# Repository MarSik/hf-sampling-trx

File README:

HF RX based on QSD and class E TX
---------------------------------

Important components:

Si570 - any frequency I2C controlled square wave oscillator
74CBT(LV)3253 - dual 1:4 analog multiplexor
LT6231CS8 - ultra low noise (1.1nV/sqrtHz) opamp
ATXmega128A3U - 8bit micro with dual ADC and DAC
XC9572XL - CPLD, programmable logic, 3.3V

References:

- Dan Tayloe, N7VE
  Ultra Low Noise, High Performance, Zero IF Quadrature Product Detector and Preamplifier
  http://www.norcalqrp.org/files/Tayloe_mixer_x3a.pdf

- Gerald Youngblood, AC5OG
  A Software-Defined Radio for the Masses
  http://www.flex-radio.com/data/doc/qex1.pdf
  http://www.flex-radio.com/data/doc/qex2.pdf
  http://www.flex-radio.com/data/doc/qex3.pdf
  http://www.flex-radio.com/data/doc/qex4.pdf

- YU1LM
  HF - 6m band pass filters
  http://yu1lm.qrpradio.com/HF-6m%20BP%20YU1LM%20ver2.pdf

- Dan Tayloe, N7VE
  Class E Amplifiers - NorCal QRP Club
  http://www.norcalqrp.org/files/class_e_amplifiers.pdf

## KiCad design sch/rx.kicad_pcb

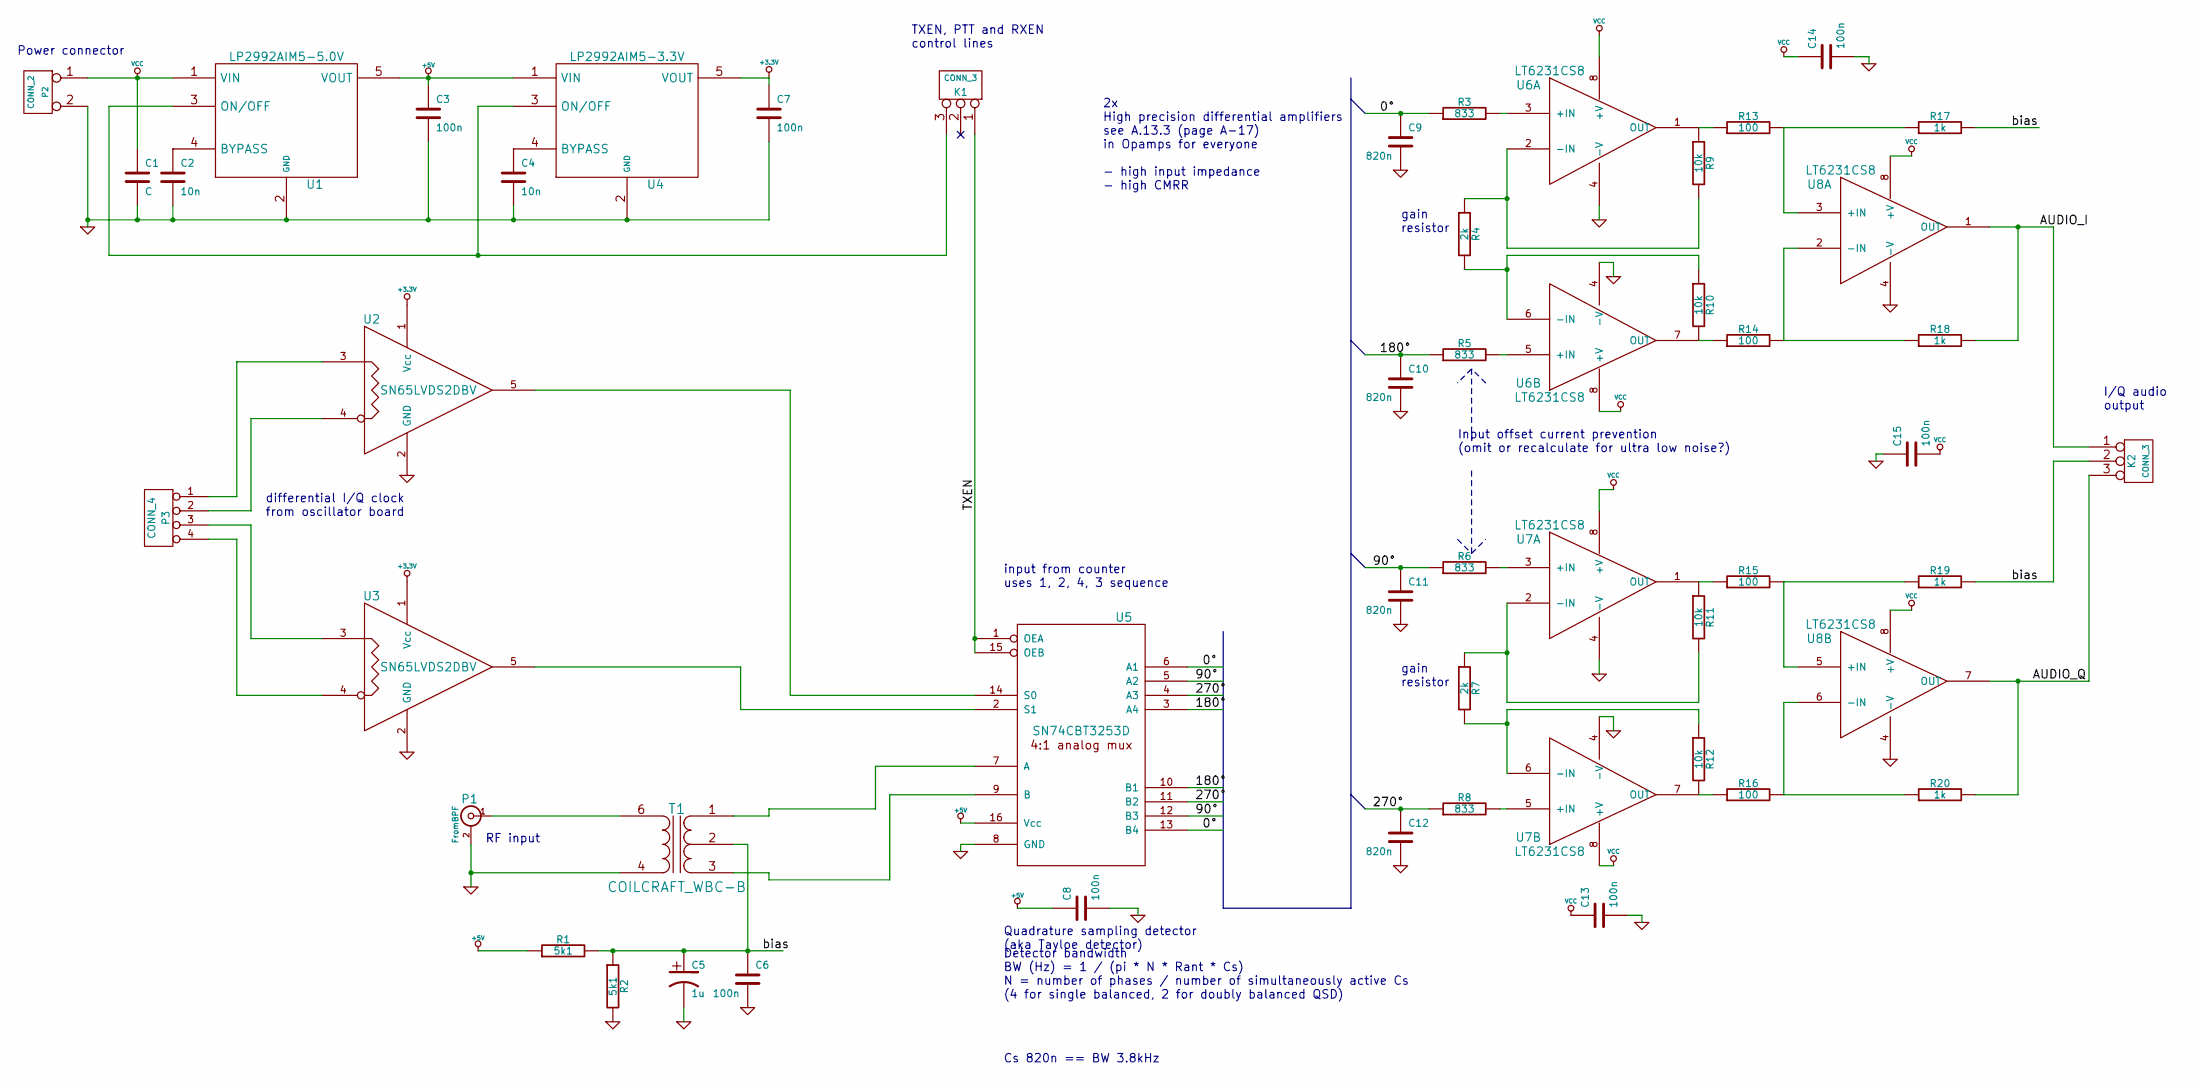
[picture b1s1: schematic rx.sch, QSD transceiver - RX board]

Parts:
C1: C
C2, C4: 10n
C3, C6, C7, C8, C13, C14, C15: 100n
C5: 1u
C9, C10, C11, C12: 820n
K1, K2: CONN_3
P1: FromBPF
P2: CONN_2
P3: CONN_4
R1, R2: 5k1
R3, R5, R6, R8: 833
R4, R7: 2k
R9, R10, R11, R12: 10k
R13, R14, R15, R16: 100
R17, R18, R19, R20: 1k
T1: COILCRAFT_WBC-B
U1: LP2992AIM5-5.0V; SOT23-5; Part Number LP2992AIM5-3.3CT-ND
U2, U3: SN65LVDS2DBV
U4: LP2992AIM5-3.3V; SOT23-5; Part Number LP2992AIM5-3.3CT-ND
U5: SN74CBT3253D
U6, U7, U8: LT6231CS8

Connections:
+3.3V: C7.1, U2.1 (Vcc), U3.1 (Vcc), U4.5 (VOUT)
+5V: C3.1, C8.1, R1.1, U1.5 (VOUT), U4.1 (VIN), U5.16 (Vcc)
/0°: C9.1, R3.1, U5.6 (A1), U5.13 (B4)
/90°: C11.1, R6.1, U5.5 (A2), U5.12 (B3)
/180°: C10.1, R5.1, U5.3 (A4), U5.10 (B1)
/270°: C12.1, R8.1, U5.4 (A3), U5.11 (B2)
/AUDIO_I: K2.1, R18.2, U8.1 (OUT)
/AUDIO_Q: K2.3, R20.2, U8.7 (OUT)
/TXEN: K1.1, U5.1 (OEA), U5.15 (OEB)
/bias: C5.1, C6.1, K2.2 (PM), R1.2, R2.1, R17.2, R19.2, T1.2 (PM)
GND: C1.2, C2.2, C3.2, C4.2, C5.2, C6.2, C7.2, C8.2, C9.2, C10.2, C11.2, C12.2, C13.2, C14.2, C15.1, P1.2 (Ext), P2.2 (PM), R2.2, T1.4 (S1), U1.2 (GND), U2.2 (GND), U3.2 (GND), U4.2 (GND), U5.8 (GND), U6.4 (-V), U7.4 (-V), U8.4 (-V)
unnamed: T1.1 (PR1), U5.7 (A)
unnamed: R16.2, R20.1, U8.6 (-IN)
unnamed: R15.2, R19.1, U8.5 (+IN)
unnamed: R7.2, R12.1, U7.6 (-IN)
unnamed: R11.1, R15.1, U7.1 (OUT)
unnamed: R12.2, R16.1, U7.7 (OUT)
unnamed: R5.2, U6.5 (+IN)
unnamed: R13.2, R17.1, U8.3 (+IN)
unnamed: R10.2, R14.1, U6.7 (OUT)
unnamed: C2.1, U1.4 (BYPASS)
unnamed: R4.2, R10.1, U6.6 (-IN)
unnamed: R3.2, U6.3 (+IN)
unnamed: R9.1, R13.1, U6.1 (OUT)
unnamed: R14.2, R18.1, U8.2 (-IN)
unnamed: R4.1, R9.2, U6.2 (-IN)
unnamed: P3.4, U3.4
unnamed: P3.3, U3.3
unnamed: P3.1, U2.3
unnamed: P3.2, U2.4
unnamed: U2.5, U5.14 (S0)
unnamed: P1.1 (In), T1.6 (S2)
unnamed: R8.2, U7.5 (+IN)
unnamed: R6.2, U7.3 (+IN)
unnamed: R7.1, R11.2, U7.2 (-IN)
unnamed: U3.5, U5.2 (S1)
unnamed: K1.3, U1.3 (ON/OFF), U4.3 (ON/OFF)
unnamed: T1.3 (PR2), U5.9 (B)
unnamed: C4.1, U4.4 (BYPASS)
VCC: C1.1, C13.1, C14.1, C15.2, P2.1, U1.1 (VIN), U6.8 (+V), U7.8 (+V), U8.8 (+V)

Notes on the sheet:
Quadrature sampling detector (aka Tayloe detector)
gain resistor
Input offset current prevention (omit or recalculate for ultra low noise?)
2x High precision differential amplifiers see A.13.3 (page A-17) in Opamps for everyone - high input impedance - high CMRR
input from counter uses 1, 2, 4, 3 sequence
differential I/Q clock from oscillator board
Power connector
RF input
I/Q audio output
TXEN, PTT and RXEN control lines
Detector bandwidth BW (Hz) = 1 / (pi * N * Rant * Cs) N = number of phases / number of simultaneously active Cs (4 for single balanced, 2 for doubly balanced QSD)
Cs 820n == BW 3.8kHz

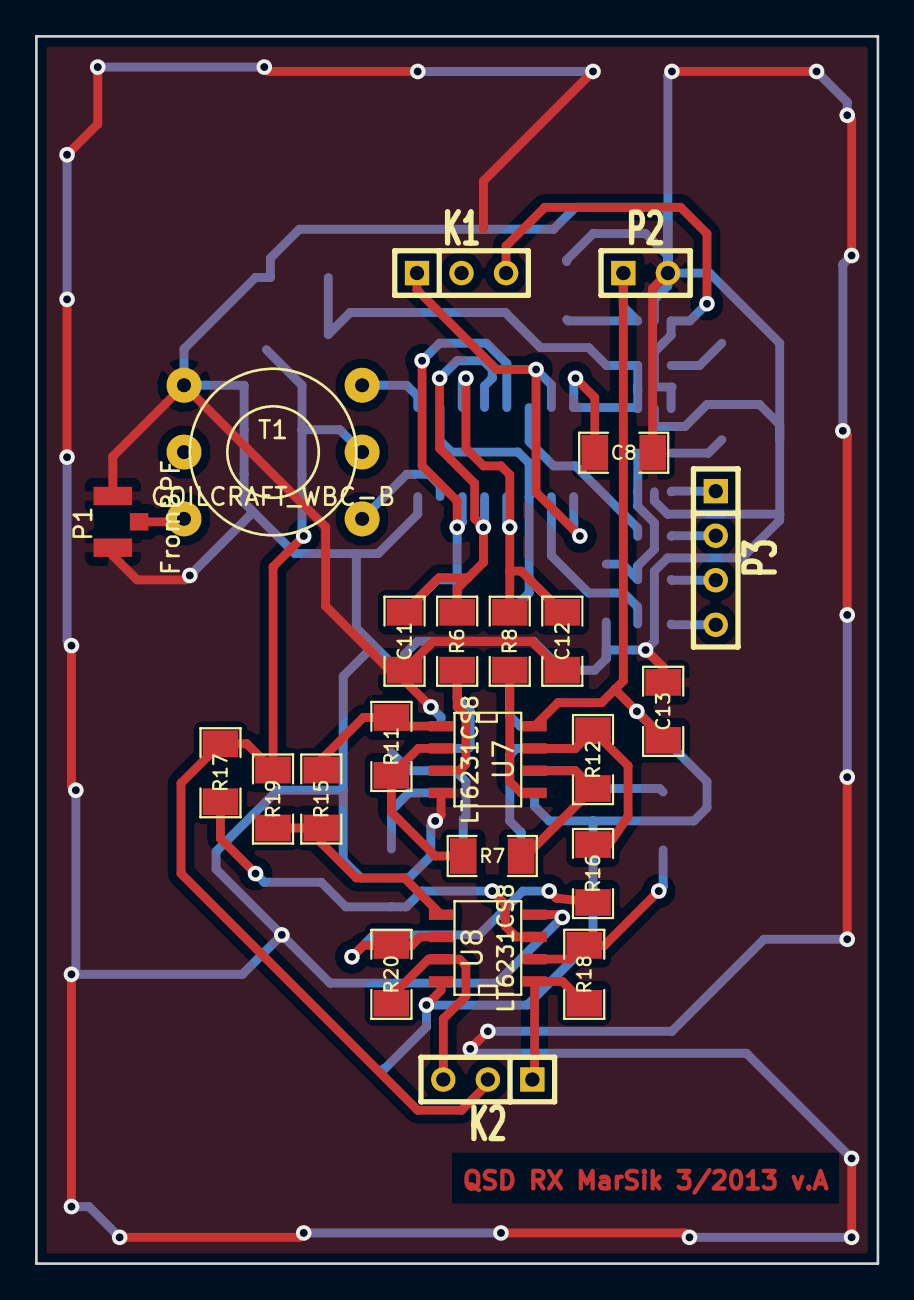
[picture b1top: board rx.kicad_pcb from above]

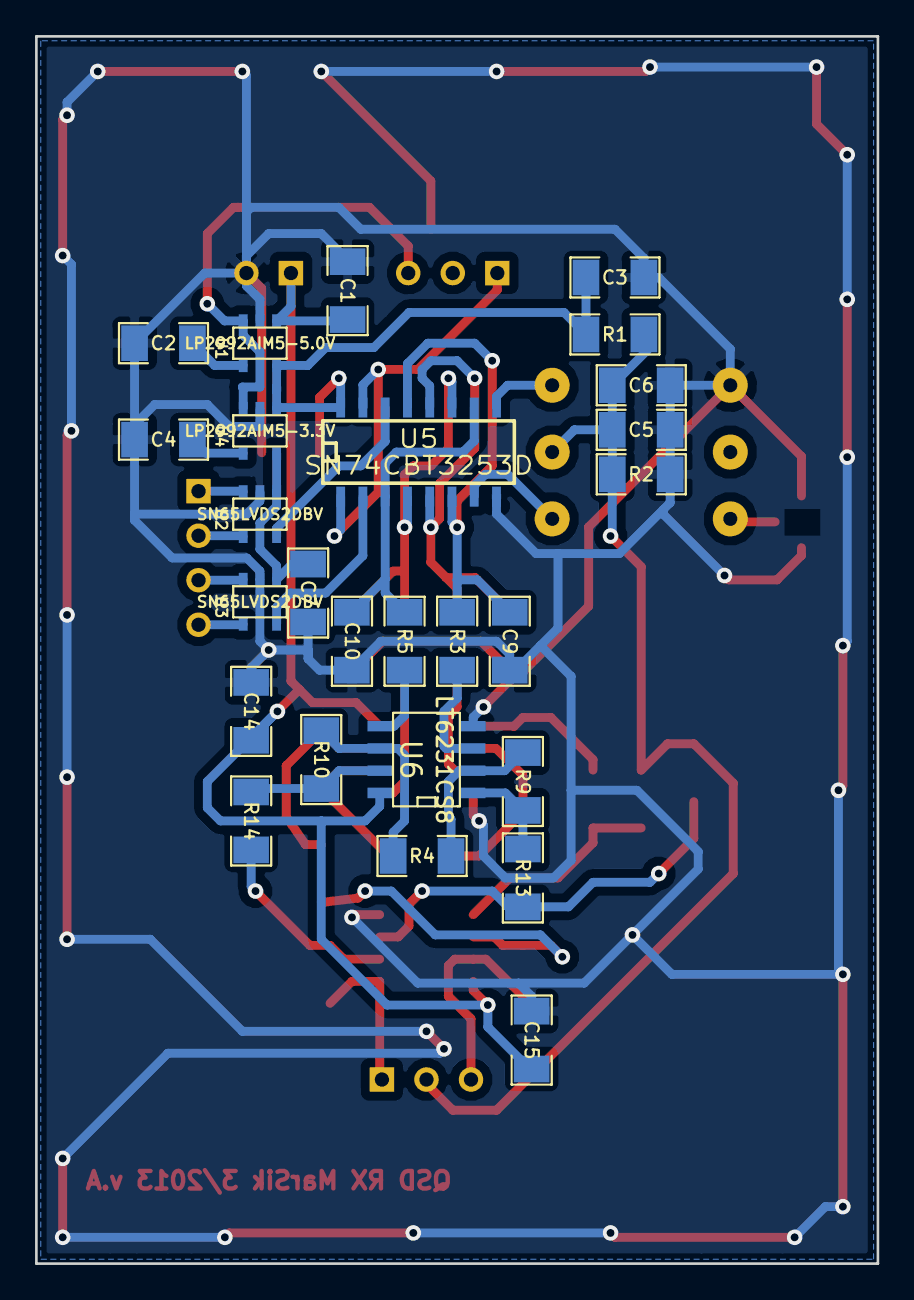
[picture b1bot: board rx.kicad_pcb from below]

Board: 2 copper layers, 48.0 x 70.0 mm, 49 parts (26 on the bottom side), 40 nets.

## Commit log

2012-06-30 Inital version
2012-06-30 add FIN1002 buffer for LVDS variant of Si570
2012-11-26 Split the RX, TX, CPU and interface boards + make the TRX more modular
2013-03-17 Add models and updated schematics
2013-03-24 Prototype RX pcb
2013-03-24 Fill more board space with ground in RX
2013-03-25 Gerber and pdf files for RX board (for manufacturing at home)
2013-03-25 Add capacitors to RX board schematics
